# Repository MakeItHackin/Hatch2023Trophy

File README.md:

# Hatch2023Trophy

Overview of the trophies created for the HATCH 2023 Winners

Thanks for visiting this page to learn more about your HATCH trophy!

View my YouTube video for a quick overview and demo:  This video was made for the 2022 Trophy, but is nearly identical.  
https://youtu.be/y4QBiJtTjaM

The trophy uses open source code and hardware, so please hack it to make it do what you want. It comes loaded with some demo code to test each of the components.

There may be updates to this page, but if you have any questions or comments, please initiate a "Issue" on github, and I will answer as soon as I can.

With the demo code loaded, the trophy will boot to the 'menu' screen.
Press the main button scroll through the menu.
When you go into the 'Demo Mode' Function, the program will loop forever. To exit the loop, just press the reset button.

The following functions are loaded with the demo software:
Lite Sense (view the analog signal from the light sensor. Minimum is ~888 (dark) and Maximum is ~1000 (very very bright))
Demo Mode (scrolls through all features, sensors, and animations)

The trophies feature the following major components:
ATTINY-85 Microcontroller
128x32 Pixel OLED display
Neopixel (WS2812v3) RGB LEDs
Light Sensor
18650 Battery, along with charging circuit (micro USB)
Pinout for all 8 pins on the microcontroller, so you can program it or add other features.

How to set up Arduino:
https://www.arduino.cc/en/Guide/ArduinoUno

How to Program the trophy (Arduino as ISP):
The trophy contains an ATTINY85 Microcontroller and can be programed unsing an arduino board, like the arduino uno.  
https://create.arduino.cc/projecthub/arjun/programming-attiny85-with-arduino-uno-afb829

Pinout for the ATTINY-85 eight-pin breakout:
-----------
| 1 2 3 4 |
| 5 6 7 8 |
-----------
PINs 1,2,3,5,6,7 are used for uploading code via ISCP to the ATTINY-85

1 - 
2 - 
3 - 
4 - 
5 - 
6 - 
7 - 
8 - 

It may be possible to program the trophy using a micro USB cable and the Micronucleus bootloader.  I have included the circuitry for that, but haven't tried to configure it.  It seems like most modern computers have trouble with it.  But if you want that functionality, give it a try!  For advanced users only.

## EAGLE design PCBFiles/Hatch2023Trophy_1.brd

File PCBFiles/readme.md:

These are the PCB files for the trophies. They were created in Eagle.

The SCH and BRD are the eagle files and the zip file is the gerber file set used to order the PCBs

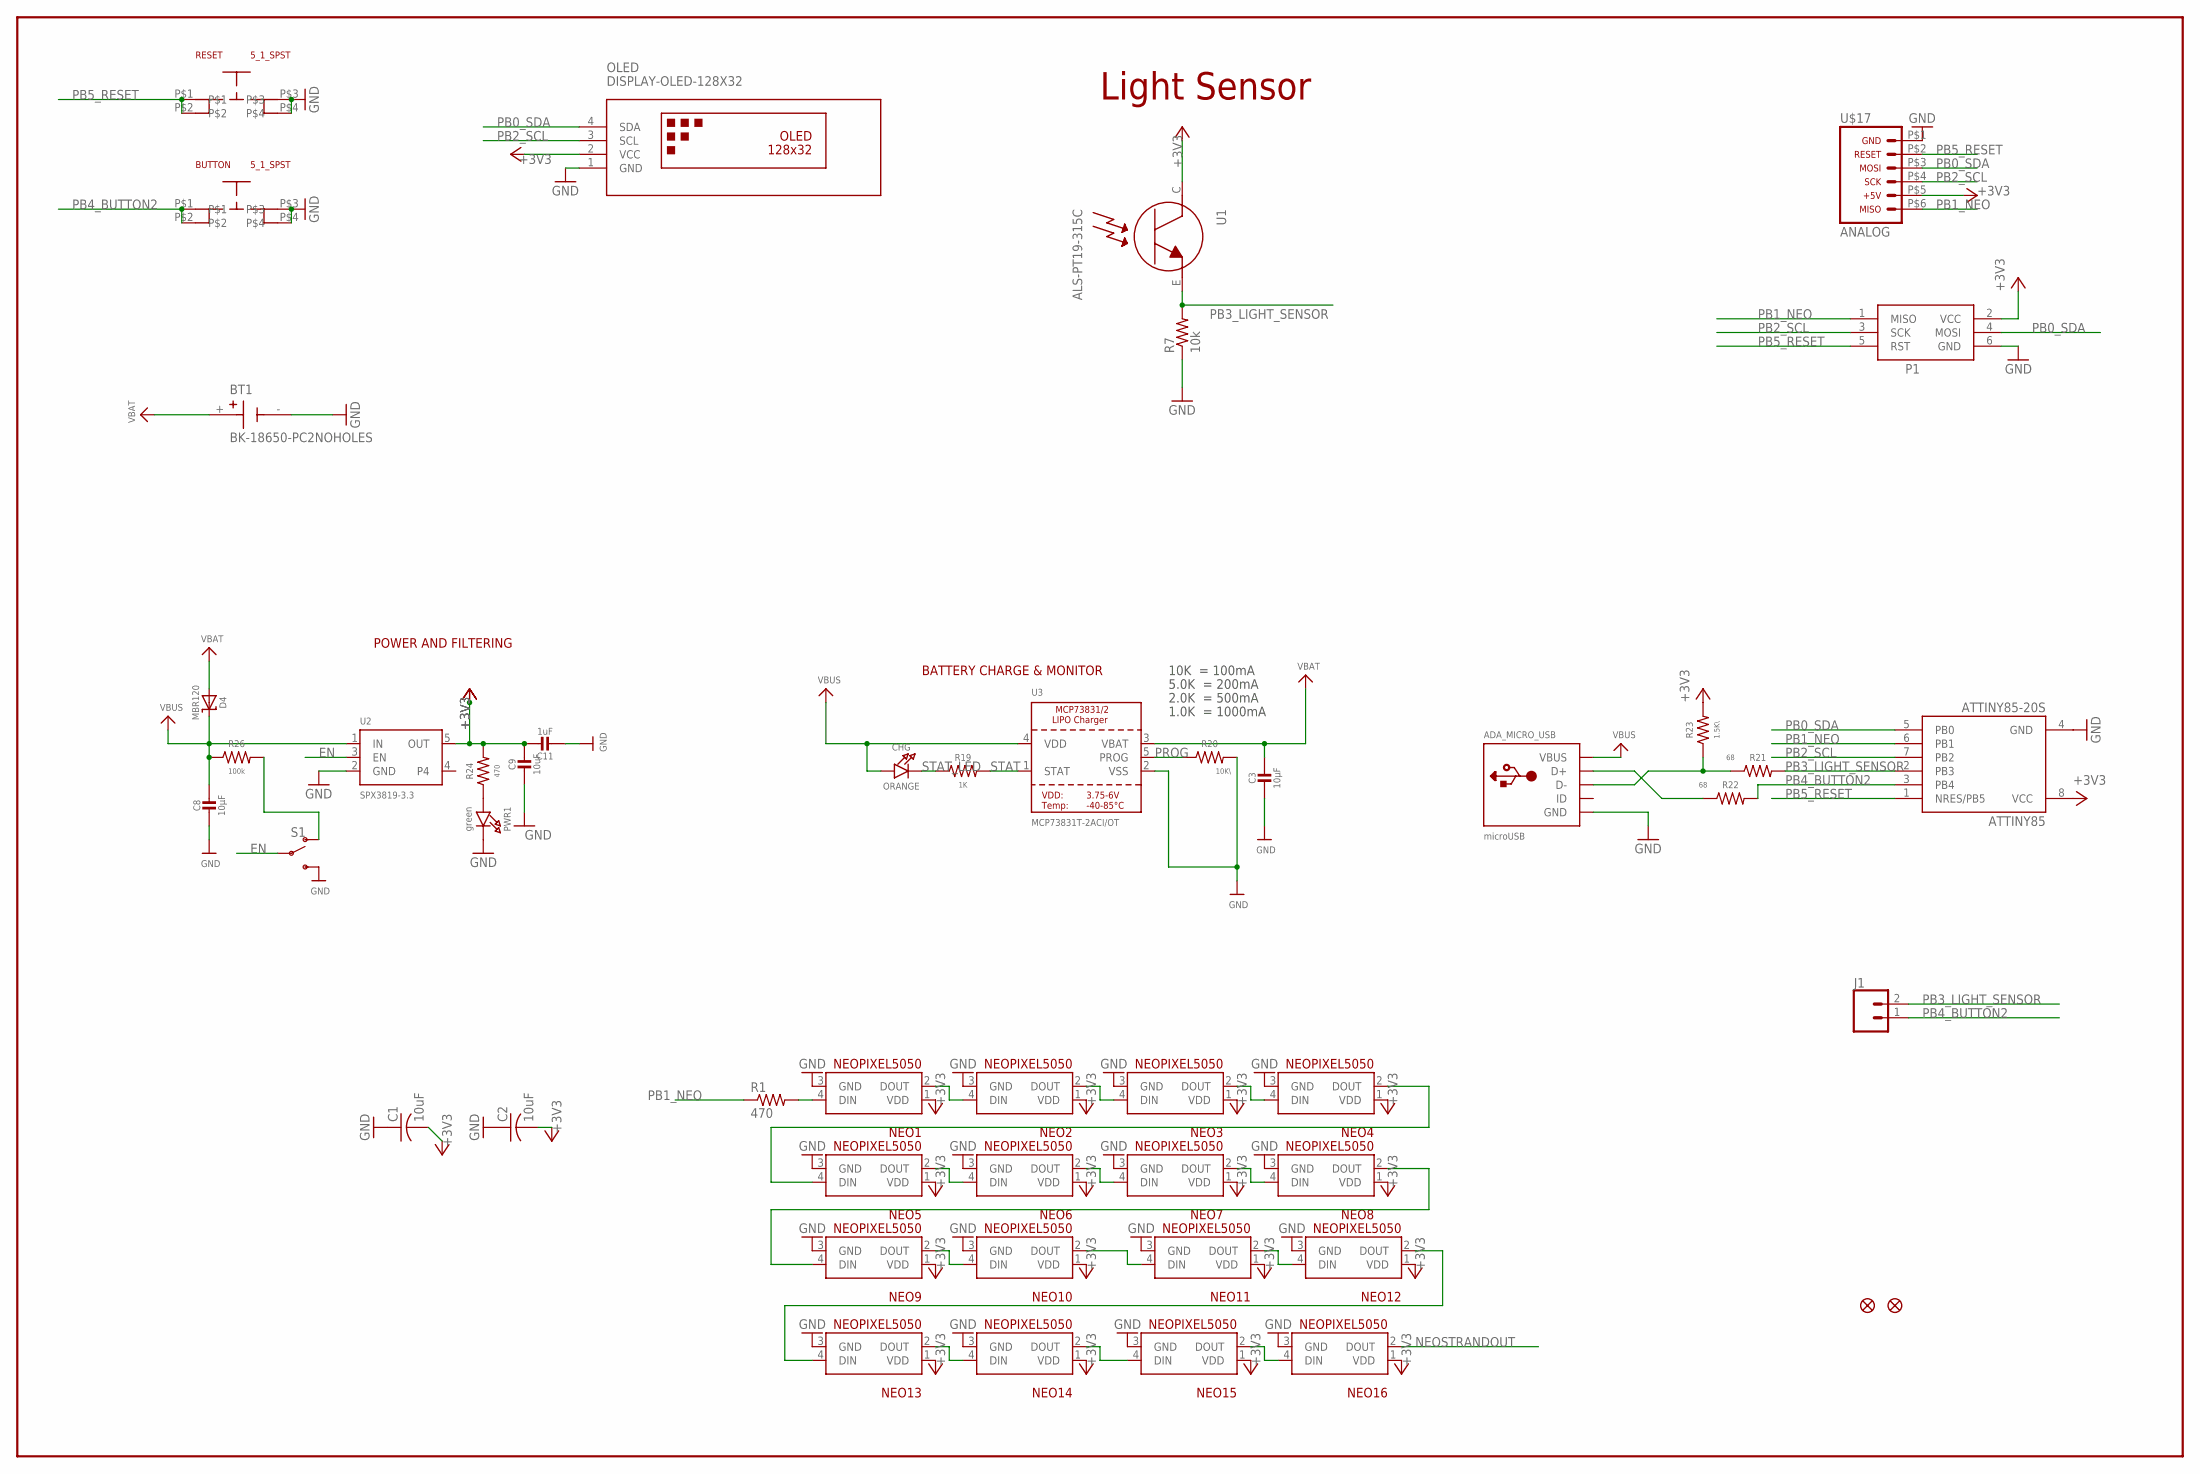
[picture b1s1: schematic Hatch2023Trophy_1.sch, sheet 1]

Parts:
ADA_MICRO_USB: microUSB; 4UCONN_20329_V2
ATTINY85: ATTINY85-20S; SOIC8_EIAJ_208MIL
BT1: BK-18650-PC2NOHOLES; BAT_BK-18650-PC2_NOHOLES
BUTTON: 5_1_SPST
C1, C2: 10uF; C0805
C3, C8: 10µF; 0805-NO@1
C9: 10uF; 0805-NO@1
C11: 1uF; 0805-NO@1
CHG: ORANGE; CHIPLED_0805_NOOUTLINE
D4: MBR120; SOD-123
J1: CONN_02; 1X02
NEO1, NEO2, NEO3, NEO4, NEO5, NEO6, NEO7, NEO8, NEO9, NEO10, NEO11, NEO12, NEO13, NEO14, NEO15, NEO16: NEOPIXEL5050
OLED: DISPLAY-OLED-128X32
P1: AVRISP-6; AVRISP
PWR1: green; CHIPLED_0805_NOOUTLINE
R1, R24: 470; R0805
R7: 10k; R0805
R19: 1K; R0805
R20: 10K\; R0805
R21, R22: 68; R0805
R23: 1.5K\; R0805
R26: 100k; R0805
RESET: 5_1_SPST
S1: SWITCH-SPDT-SMD-AYZ0202; SWITCH_DPDT_SMD_AYZ0202
U1: ALS-PT19-315C
U2: SPX3819-3.3; SOT23-5
U3: MCP73831T-2ACI/OT; SOT23-5
U$17: ICSP_FLATSMD_2X3; CONN-SMD-2X3
U$34, U$35: FIDUCIAL_1MM

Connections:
+3V3: ATTINY85.8 (VCC), C1.2, C2.2, C9.1, C11.1, NEO1.1 (VDD), NEO2.1 (VDD), NEO3.1 (VDD), NEO4.1 (VDD), NEO5.1 (VDD), NEO6.1 (VDD), NEO7.1 (VDD), NEO8.1 (VDD), NEO9.1 (VDD), NEO10.1 (VDD), NEO11.1 (VDD), NEO12.1 (VDD), NEO13.1 (VDD), NEO14.1 (VDD), NEO15.1 (VDD), NEO16.1 (VDD), OLED.2 (VCC), P1.2 (VCC), R23.2, R24.2, U1.C, U2.5 (OUT), U$17.P$5 (5)
D+: ADA_MICRO_USB.D+, R22.1
D-: ADA_MICRO_USB.D-, R21.1, R23.1
EN: S1.2, U2.3 (EN)
GND: ADA_MICRO_USB.BASE@1 (GND), ADA_MICRO_USB.BASE@2 (GND), ADA_MICRO_USB.GND, ADA_MICRO_USB.SPRT@1 (GND), ADA_MICRO_USB.SPRT@2 (GND), ADA_MICRO_USB.SPRT@3 (GND), ADA_MICRO_USB.SPRT@4 (GND), ATTINY85.4 (GND), BT1.-, BUTTON.P$3, BUTTON.P$4, C1.1, C2.1, C3.2, C8.2, C9.2, C11.2, NEO1.3 (GND), NEO2.3 (GND), NEO3.3 (GND), NEO4.3 (GND), NEO5.3 (GND), NEO6.3 (GND), NEO7.3 (GND), NEO8.3 (GND), NEO9.3 (GND), NEO10.3 (GND), NEO11.3 (GND), NEO12.3 (GND), NEO13.3 (GND), NEO14.3 (GND), NEO15.3 (GND), NEO16.3 (GND), OLED.1 (GND), P1.6 (GND), PWR1.C, R7.1, R20.2, RESET.P$3, RESET.P$4, S1.3 (S), U2.2 (GND), U3.2 (VSS), U$17.P$1 (1)
unnamed: NEO13.2 (DOUT), NEO14.4 (DIN)
unnamed: NEO11.2 (DOUT), NEO12.4 (DIN)
unnamed: NEO12.2 (DOUT), NEO13.4 (DIN)
unnamed: NEO14.2 (DOUT), NEO15.4 (DIN)
unnamed: NEO15.2 (DOUT), NEO16.4 (DIN)
unnamed: NEO4.2 (DOUT), NEO5.4 (DIN)
unnamed: PWR1.A, R24.1
unnamed: R26.2, S1.1 (O)
unnamed: NEO1.4 (DIN), R1.2
unnamed: NEO8.2 (DOUT), NEO9.4 (DIN)
unnamed: NEO1.2 (DOUT), NEO2.4 (DIN)
unnamed: NEO2.2 (DOUT), NEO3.4 (DIN)
unnamed: NEO3.2 (DOUT), NEO4.4 (DIN)
unnamed: NEO5.2 (DOUT), NEO6.4 (DIN)
unnamed: NEO6.2 (DOUT), NEO7.4 (DIN)
unnamed: NEO7.2 (DOUT), NEO8.4 (DIN)
unnamed: NEO9.2 (DOUT), NEO10.4 (DIN)
unnamed: NEO10.2 (DOUT), NEO11.4 (DIN)
NEOSTRANDOUT: NEO16.2 (DOUT)
PB0_SDA: ATTINY85.5 (PB0), OLED.4 (SDA), P1.4 (MOSI), U$17.P$3 (3)
PB1_NEO: ATTINY85.6 (PB1), P1.1 (MISO), R1.1, U$17.P$6 (6)
PB2_SCL: ATTINY85.7 (PB2), OLED.3 (SCL), P1.3 (SCK), U$17.P$4 (4)
PB3_LIGHT_SENSOR: ATTINY85.2 (PB3), J1.2, R7.2, R21.2, U1.E
PB4_BUTTON2: ATTINY85.3 (PB4), BUTTON.P$1, BUTTON.P$2, J1.1, R22.2
PB5_RESET: ATTINY85.1 (NRES/PB5), P1.5 (RST), RESET.P$1, RESET.P$2, U$17.P$2 (2)
PROG: R20.1, U3.5 (PROG)
STAT: R19.2, U3.1 (STAT)
STAT_LED: CHG.C, R19.1
VBAT: BT1.+, C3.1, D4.A, U3.3 (VBAT)
VBUS: ADA_MICRO_USB.VBUS, C8.1, CHG.A, D4.C, R26.1, U2.1 (IN), U3.4 (VDD)

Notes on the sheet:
POWER AND FILTERING
10K = 100mA
5.0K = 200mA
2.0K = 500mA
1.0K = 1000mA
BATTERY CHARGE & MONITOR
Light Sensor

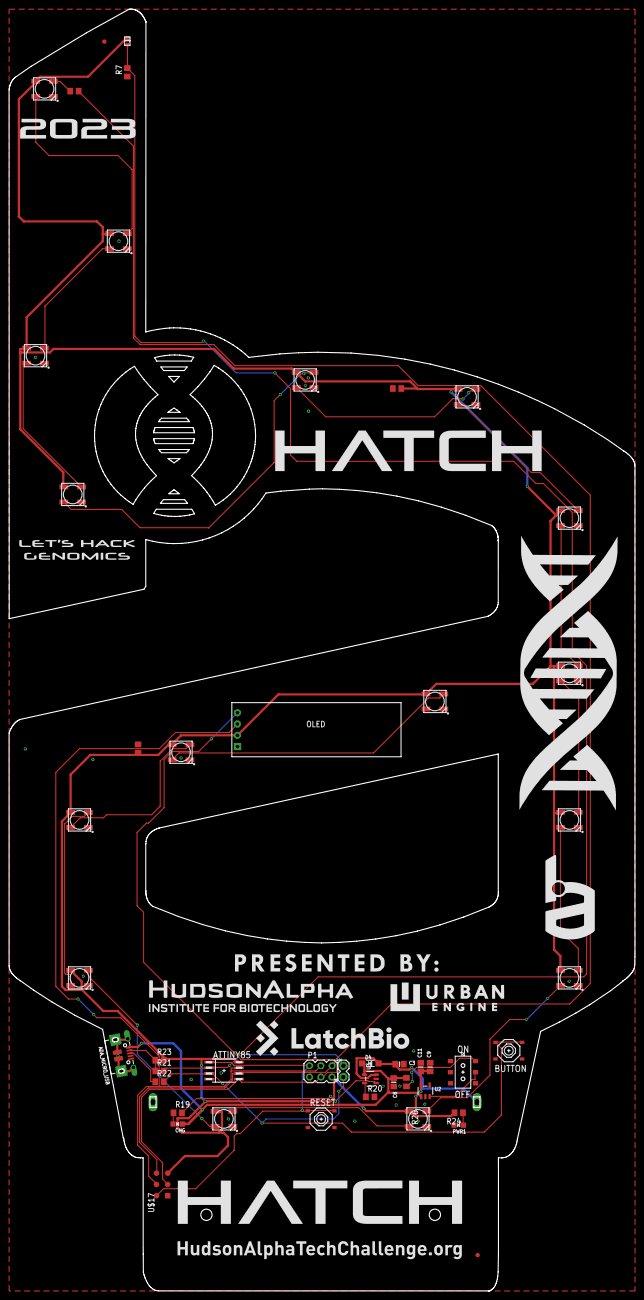
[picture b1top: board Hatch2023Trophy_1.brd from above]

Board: 2 copper layers, 140.9 x 288.6 mm, 49 parts (1 on the bottom side), 34 nets.

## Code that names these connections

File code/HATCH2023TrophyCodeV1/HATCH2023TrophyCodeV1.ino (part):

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  GND - BATTERY NEGATIVE TERMINAL
  VCC - BATTERY POSITIVE TERMINAL
  PBO - I2C BUS - SDA
  PB1 - NEOPIXEL OUT
  PB2 - I2C BUS - SCL
  PB3 - LIGHT SENSOR INPUT
  PB4 - BUTTON INPUT
  PB5 - RESET BUTTON
  
 */

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
                          

#define LIGHT_SENSOR_PIN A3  // THIS IS PB3, BUT MUST LABEL IT A3 IN ORDER FOR THE ANALOG FUNCTIONS TO WORK
int lightSensorValue = 0;


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

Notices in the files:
code/HATCH2023TrophyCodeV1/HATCH2023TrophyCodeV1.ino:
MIT license, all text above must be included in any redistribution
parts and their libraries:
microbuilder: This work is placed in the public domain, and may be freely used for commercial and non-commercial work with the following conditions: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
SparkFun-Switches: Licensing: Creative Commons ShareAlike 4.0 International - https://creativecommons.org/licenses/by-sa/4.0
